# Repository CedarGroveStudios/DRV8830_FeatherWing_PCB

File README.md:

# DRV8830_FeatherWing_PCB

## A custom motor controller and power monitor FeatherWing using the DRV8830 motor controller and INA260 or INA271 power monitor.

[DRV8830 CircuitPython Driver Class Description](https://github.com/CedarGroveStudios/DRV8830_FeatherWing_PCB/blob/main/docs/pseudo%20readthedocs%20cedargrove_drv8830.pdf)

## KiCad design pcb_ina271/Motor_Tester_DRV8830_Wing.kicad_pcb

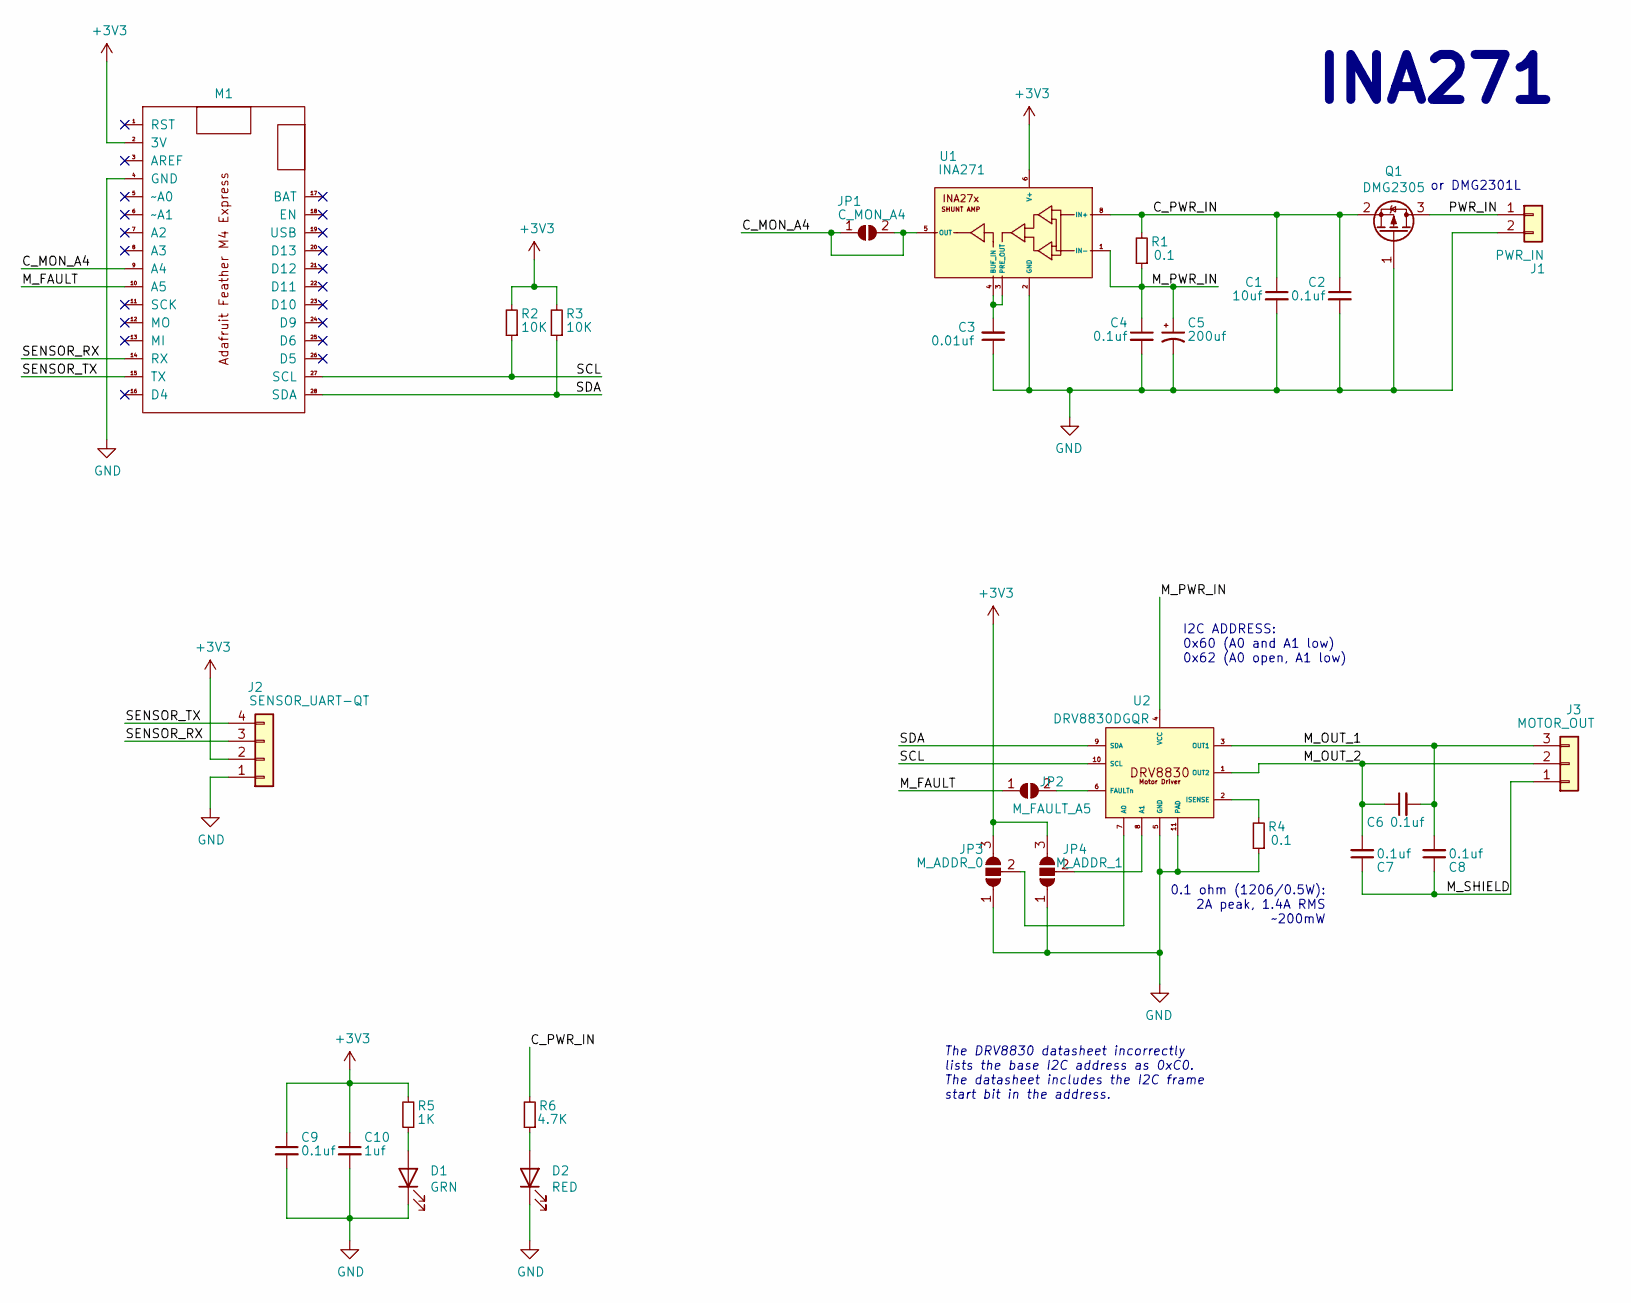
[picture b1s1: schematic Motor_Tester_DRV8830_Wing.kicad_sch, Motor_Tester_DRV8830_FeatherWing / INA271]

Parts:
C1: 10uf; C_0805_2012Metric
C2, C4, C6, C7, C8, C9: 0.1uf; C_0805_2012Metric
C3: 0.01uf; C_0805_2012Metric
C5: 200uf; CP_Elec_6.6x6.6
C10: 1uf; C_0805_2012Metric
D1: GRN; LED_0805_2012Metric
D2: RED; LED_0805_2012Metric
J1: PWR_IN; TerminalBlock_4Ucon_1x02_P3.50mm_Horizontal
J2: SENSOR_UART-QT; JST_SH_SM04B-SRSS-TB_1x04-1MP_P1.00mm_Horizontal
J3: MOTOR_OUT; TerminalBlock_4Ucon_1x03_P3.50mm_Horizontal
JP1: C_MON_A4; SolderJumper-2_P1.3mm_Open_TrianglePad1.0x1.5mm
JP2: M_FAULT_A5; SolderJumper-2_P1.3mm_Open_TrianglePad1.0x1.5mm
JP3: M_ADDR_0; SolderJumper-3_P1.3mm_Open_RoundedPad1.0x1.5mm
JP4: M_ADDR_1; SolderJumper-3_P1.3mm_Open_RoundedPad1.0x1.5mm
M1: Feather_M4_Express; Adafruit_Feather_M4_Express_bare
Q1: DMG2305; SOT-23
R1, R4: 0.1; R_1206_3216Metric
R2, R3: 10K; R_0805_2012Metric
R5: 1K; R_0805_2012Metric
R6: 4.7K; R_0805_2012Metric
U1: INA271; SOIC-8_3.9x4.9mm_P1.27mm
U2: DRV8830DGQR; MSOP-10-1EP_3x3mm_P0.5mm_EP1.68x1.88mm_ThermalVias

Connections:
+3V3: C9.1, C10.1, J2.2, JP3.3 (B), JP4.3 (B), M1.2 (3V), R2.2, R3.2, R5.2, U1.6 (V+)
/C_MON_A4: JP1.1 (A), JP1.2 (B), M1.9 (A4), U1.5 (OUT)
/C_PWR_IN: C1.1, C2.1, Q1.2 (S), R1.2, R6.2, U1.8 (IN+)
/M_FAULT: JP2.1 (A), M1.10 (A5)
/M_OUT_1: C6.2, C8.2, J3.3, U2.3 (OUT1)
/M_OUT_2: C6.1, C7.2, J3.2, U2.1 (OUT2)
/M_PWR_IN: C4.1, C5.1, R1.1, U1.1 (IN-), U2.4 (VCC)
/M_SHIELD: C7.1, C8.1, J3.1
/PWR_IN: J1.1, Q1.3 (D)
/SCL: M1.27 (SCL), R2.1, U2.10 (SCL)
/SDA: M1.28 (SDA), R3.1, U2.9 (SDA)
/SENSOR_RX: J2.3, M1.14 (RX)
/SENSOR_TX: J2.4, M1.15 (TX)
GND: C1.2, C2.2, C3.1, C4.2, C5.2, C9.2, C10.2, D1.1 (K), D2.1 (K), J1.2, J2.1, JP3.1 (A), JP4.1 (A), M1.4 (GND), Q1.1 (G), R4.1, U1.2 (GND), U2.5 (GND), U2.11 (PAD)
unnamed: C3.2, U1.3 (PRE_OUT), U1.4 (BUF_IN)
unnamed: D1.2 (A), R5.1
unnamed: D2.2 (A), R6.1
unnamed: JP2.2 (B), U2.6 (FAULTn)
unnamed: JP3.2 (C), U2.7 (A0)
unnamed: JP4.2 (C), U2.8 (A1)
unnamed: R4.2, U2.2 (ISENSE)

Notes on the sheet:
The DRV8830 datasheet incorrectly lists the base I2C address as 0xC0. The datasheet includes the I2C frame start bit in the address.
I2C ADDRESS: 0x60 (A0 and A1 low) 0x62 (A0 open, A1 low)
INA271
0.1 ohm (1206/0.5W): 2A peak, 1.4A RMS ~200mW
or DMG2301L

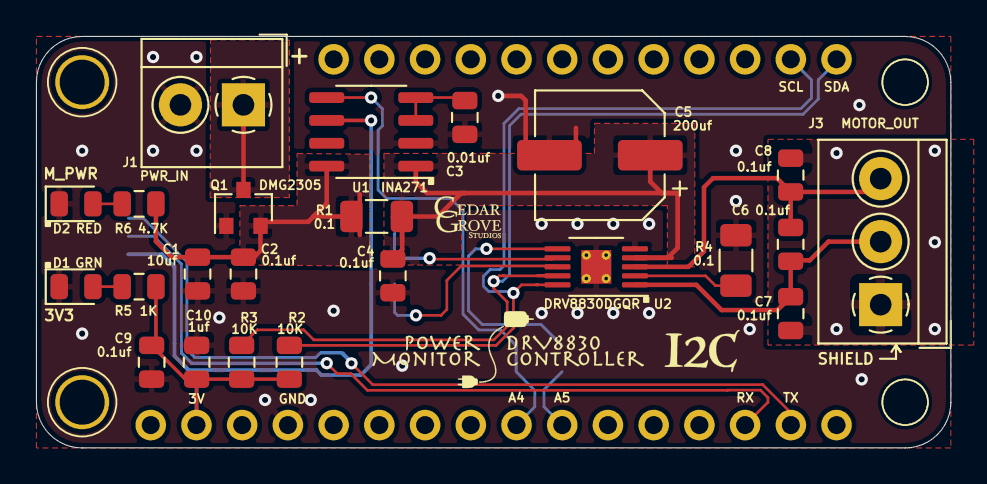
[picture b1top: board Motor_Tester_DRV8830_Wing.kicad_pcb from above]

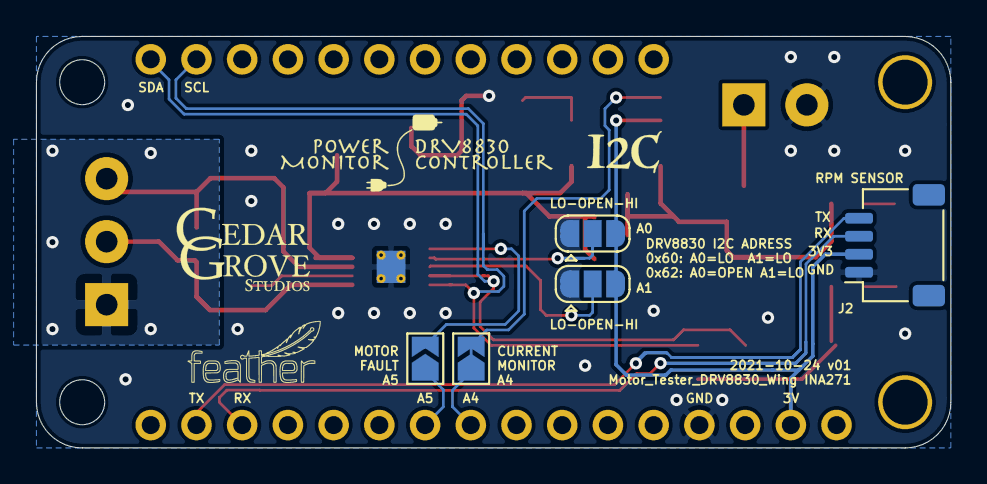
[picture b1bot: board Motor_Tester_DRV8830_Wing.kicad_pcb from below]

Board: 2 copper layers, 50.8 x 22.9 mm, 29 parts (5 on the bottom side), 21 nets.

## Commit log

2022-04-24 initial repo load
2022-04-25 rename old driver class file as "orig"
2022-04-27 update with bundle-compatible file format
2022-09-02 update license
2022-09-14 update docs, example
2022-09-16 update version string
2022-09-23 update docs
